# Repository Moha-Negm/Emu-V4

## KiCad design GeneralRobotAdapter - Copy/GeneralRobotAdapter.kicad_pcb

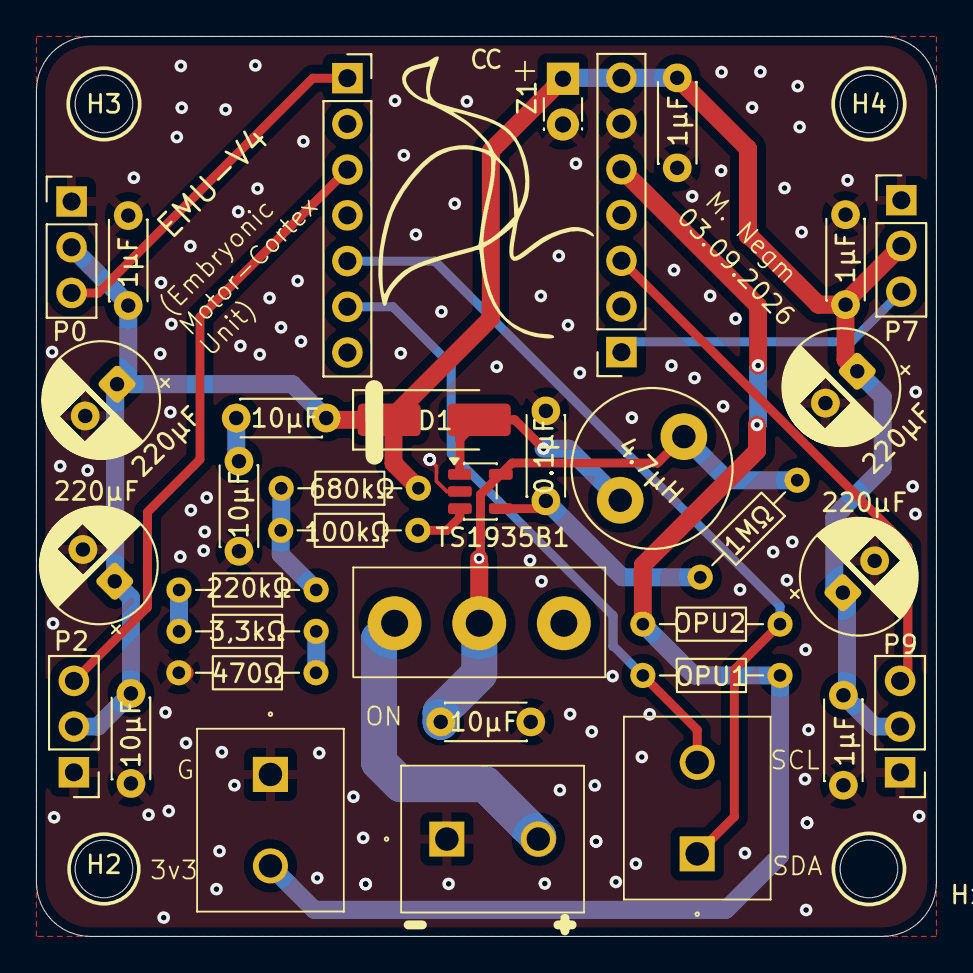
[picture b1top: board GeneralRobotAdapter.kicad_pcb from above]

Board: 2 copper layers, 50.0 x 50.0 mm, 39 parts (0 on the bottom side), 18 nets.

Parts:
0.1µF: 0.1µF; C_Disc_D4.3mm_W1.9mm_P5.00mm
1MΩ: 1MΩ; R_Axial_DIN0204_L3.6mm_D1.6mm_P7.62mm_Horizontal
1µF, 1µF#2, 1µF#3, 1µF#4: 1µF; C_Disc_D4.3mm_W1.9mm_P5.00mm
3,3kΩ: 3,3kΩ; R_Axial_DIN0204_L3.6mm_D1.6mm_P7.62mm_Horizontal
4.7µH: 4.7µH; L_Radial_D8.7mm_P5.00mm_Fastron_07HCP
10µF, 10µF#2, 10µF#3, 10µF#4: 10µF; C_Disc_D4.3mm_W1.9mm_P5.00mm
100kΩ: 100kΩ?; R_Axial_DIN0204_L3.6mm_D1.6mm_P7.62mm_Horizontal
220kΩ: 220kΩ; R_Axial_DIN0204_L3.6mm_D1.6mm_P7.62mm_Horizontal
220µF, 220µF#2, 220µF#3, 220µF#4: 220µF; CP_Radial_D6.3mm_P2.50mm
470Ω: 470Ω; R_Axial_DIN0204_L3.6mm_D1.6mm_P7.62mm_Horizontal
680kΩ: 680kΩ; R_Axial_DIN0204_L3.6mm_D1.6mm_P7.62mm_Horizontal
C: Right Docker; PinSocket_1x07_P2.54mm_Vertical
C#2: Left Docker; PinSocket_1x07_P2.54mm_Vertical
D1: D_Schottky; D_SMA_Handsoldering
H1, H2, H3, H4: M3; MountingHole_3.2mm_M3
J10, J11, J12: Conn_01x02; 1729128
ON: SW_Nidec_CAS-120A1; Korean Switch
OPU1, OPU2: R; R_Axial_DIN0204_L3.6mm_D1.6mm_P7.62mm_Horizontal
P0: Servo Header 3; PinHeader_1x03_P2.54mm_Vertical
P2: Servo Header 1; PinHeader_1x03_P2.54mm_Vertical
P7: Servo Header 2; PinHeader_1x03_P2.54mm_Vertical
P9: Servo Header 4; PinHeader_1x03_P2.54mm_Vertical
TS1935B1: SOT-23-5
Z1: D_Zener; LED_Rectangular_W3.0mm_H2.0mm

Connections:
+3.3V: C.5, J11.2, OPU1.1, OPU2.2
+5V: 1µF.1, 1µF#2.1, 1µF#3.1, 1µF#4.1, 10µF.1, 10µF#3.1, 220µF.1, 220µF#2.1, 220µF#3.1, 220µF#4.1, 680kΩ.1, C.7, D1.1 (K), P0.2, P2.2, P7.2, P9.2, Z1.1 (K)
B+: J10.2, ON.1 (C)
GND: 0.1µF.2, 1µF.2, 1µF#2.2, 1µF#3.2, 1µF#4.2, 10µF.2, 10µF#2.2, 10µF#4.2, 220µF.2, 220µF#2.2, 220µF#3.2, 220µF#4.2, 470Ω.2, C.6, J10.1, J11.1, P0.1, P2.1, P7.1, P9.1, TS1935B1.2 (GND), Z1.2 (A)
unnamed: 10µF#2.1, 10µF#3.2
unnamed: 4.7µH.2, D1.2 (A), TS1935B1.1 (SW)
unnamed: 100kΩ.2, 220kΩ.1, 680kΩ.2
unnamed: 3,3kΩ.1, 220kΩ.2
unnamed: 3,3kΩ.2, 470Ω.1
unnamed: 1MΩ.1, 4.7µH.1, 10µF#4.1, ON.2 (B), TS1935B1.5 (VCC)
unnamed: 0.1µF.1, 1MΩ.2, TS1935B1.4 (EN)
unnamed: 100kΩ.1, TS1935B1.3 (FB)
SCl: C#2.6, J12.2, OPU1.2
SDA: C#2.5, J12.1, OPU2.1
Servo 1: C#2.1, P0.3
Servo 2: C#2.3, P2.3
Servo 3: C.3, P9.3
Servo 4: C.1, P7.3
